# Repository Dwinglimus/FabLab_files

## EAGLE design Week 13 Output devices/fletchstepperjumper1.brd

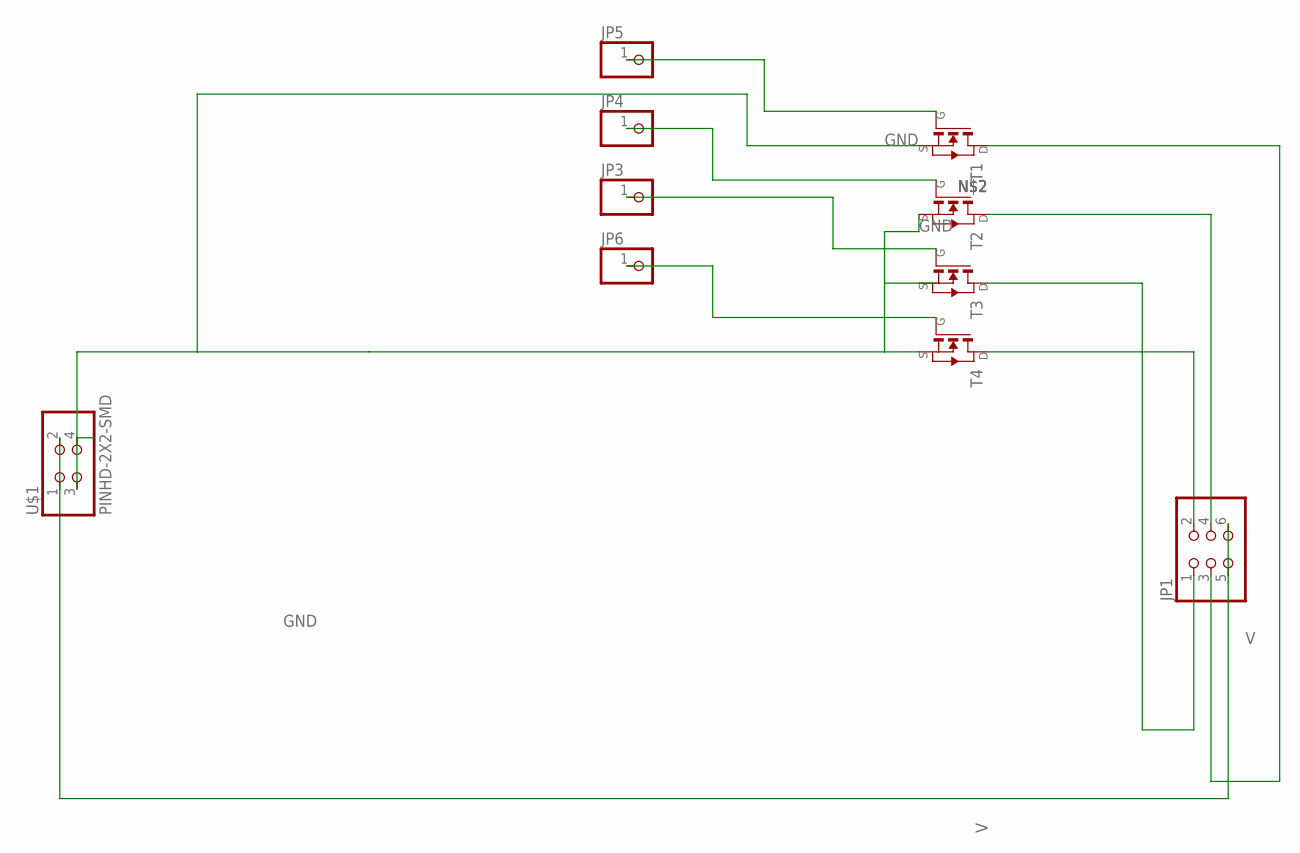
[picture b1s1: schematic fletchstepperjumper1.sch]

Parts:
JP1: PINHD-2X3-SMD; 2X03SMD
JP3, JP4, JP5, JP6: PINHD-1X1; 1X01
T1, T2, T3, T4: NMOSFETSOT23; SOT-23
U$1: PINHD-2X2-SMD; 2X02SMD

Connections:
GND: T1.2 (S), T2.2 (S), T4.2 (S), U$1.3
unnamed: JP6.1, T4.3 (G)
unnamed: JP4.1, T2.3 (G)
unnamed: JP3.1, T3.3 (G)
unnamed: JP1.2, T4.1 (D)
unnamed: JP1.4, T2.1 (D)
unnamed: JP1.1, T3.1 (D)
unnamed: JP1.3, T1.1 (D)
unnamed: JP5.1, T1.3 (G)
V: JP1.5, JP1.6, U$1.1, U$1.2

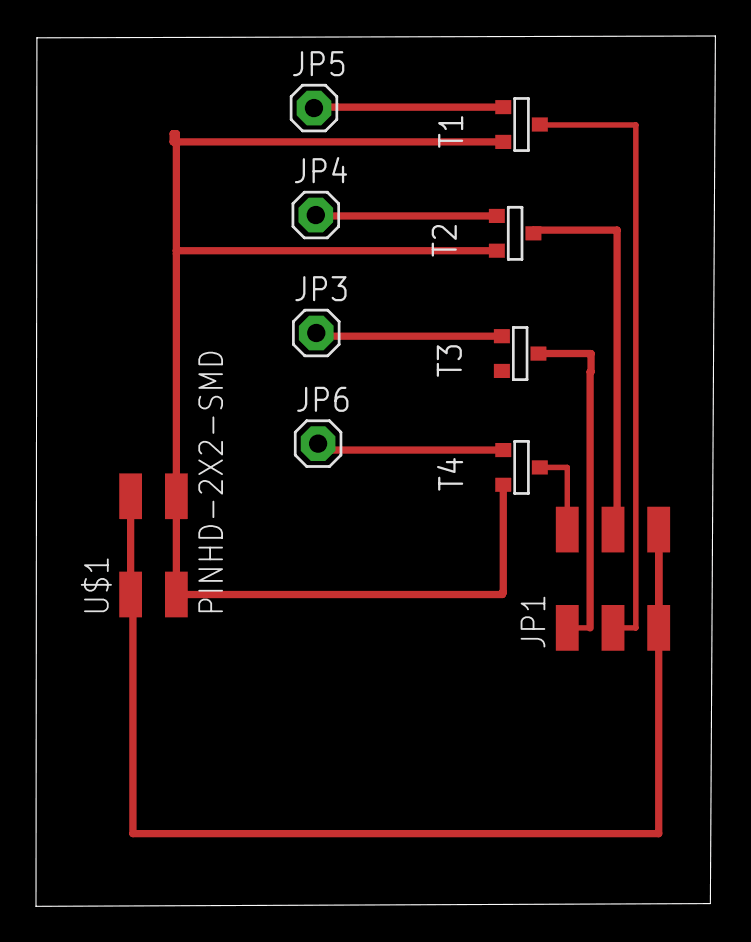
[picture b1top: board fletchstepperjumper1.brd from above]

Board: 2 copper layers, 37.7 x 48.4 mm, 10 parts (0 on the bottom side), 10 nets.

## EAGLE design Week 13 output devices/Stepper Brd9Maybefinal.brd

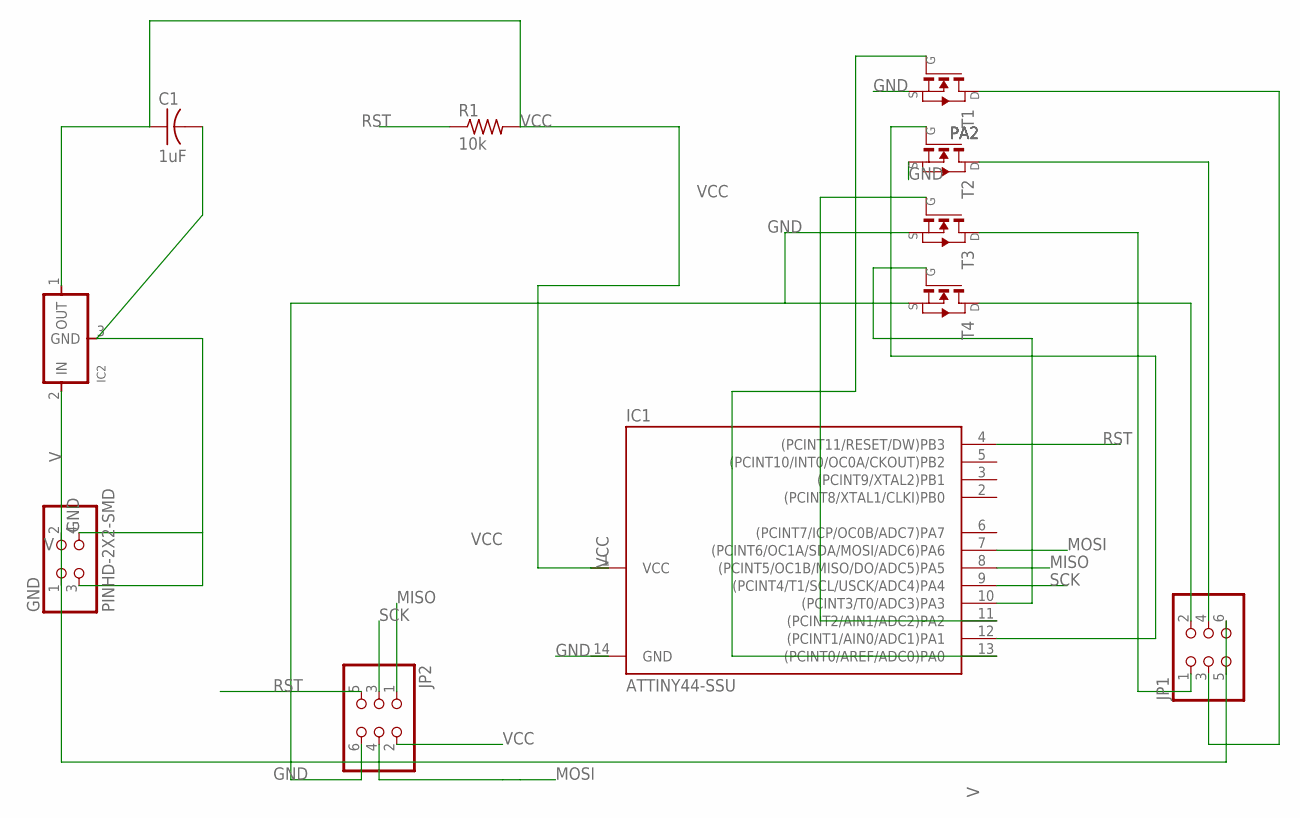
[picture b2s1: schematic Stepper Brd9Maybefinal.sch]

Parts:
C1: 1uF; C1206FAB
GND: PINHD-2X2-SMD; 2X02SMD
IC1: ATTINY44-SSU; SOIC14
IC2: REGULATORSOT23; SOT23
JP1, JP2: PINHD-2X3-SMD; 2X03SMD
R1: 10k; R1206FAB
T1, T2, T3, T4: NMOSFETSOT23; SOT-23

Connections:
GND: C1.2, GND.3, GND.4, IC1.14 (GND), IC2.3 (GND), JP2.6, T1.2 (S), T2.2 (S), T3.2 (S), T4.2 (S)
MISO: IC1.8 ((PCINT5/OC1B/MISO/DO/ADC5)PA5), JP2.1
MOSI: IC1.7 ((PCINT6/OC1A/SDA/MOSI/ADC6)PA6), JP2.4
unnamed: IC1.10 ((PCINT3/T0/ADC3)PA3), T4.3 (G)
unnamed: IC1.11 ((PCINT2/AIN1/ADC2)PA2), T3.3 (G)
unnamed: JP1.2, T4.1 (D)
unnamed: JP1.4, T2.1 (D)
unnamed: JP1.1, T3.1 (D)
unnamed: JP1.3, T1.1 (D)
unnamed: IC1.13 ((PCINT0/AREF/ADC0)PA0), T1.3 (G)
PA2: IC1.12 ((PCINT1/AIN0/ADC1)PA1), T2.3 (G)
RST: IC1.4 ((PCINT11/RESET/DW)PB3), JP2.5, R1.1
SCK: IC1.9 ((PCINT4/T1/SCL/USCK/ADC4)PA4), JP2.3
V: GND.1, GND.2, IC2.2 (IN), JP1.5, JP1.6
VCC: C1.1, IC1.1 (VCC), IC2.1 (OUT), JP2.2, R1.2

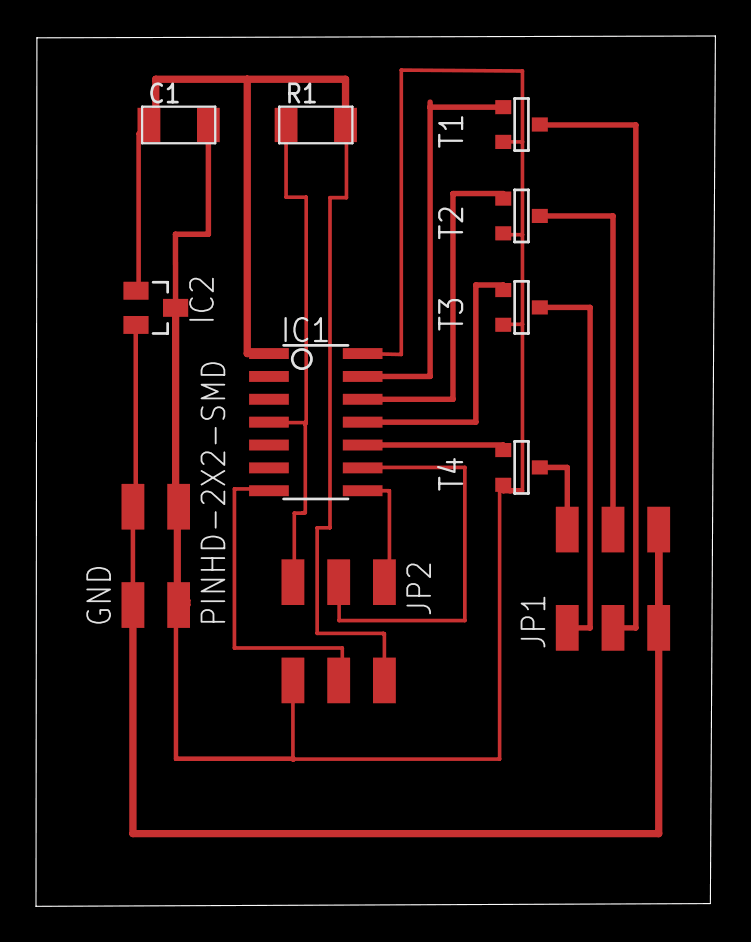
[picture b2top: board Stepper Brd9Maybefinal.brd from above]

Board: 2 copper layers, 37.7 x 48.4 mm, 11 parts (0 on the bottom side), 15 nets.

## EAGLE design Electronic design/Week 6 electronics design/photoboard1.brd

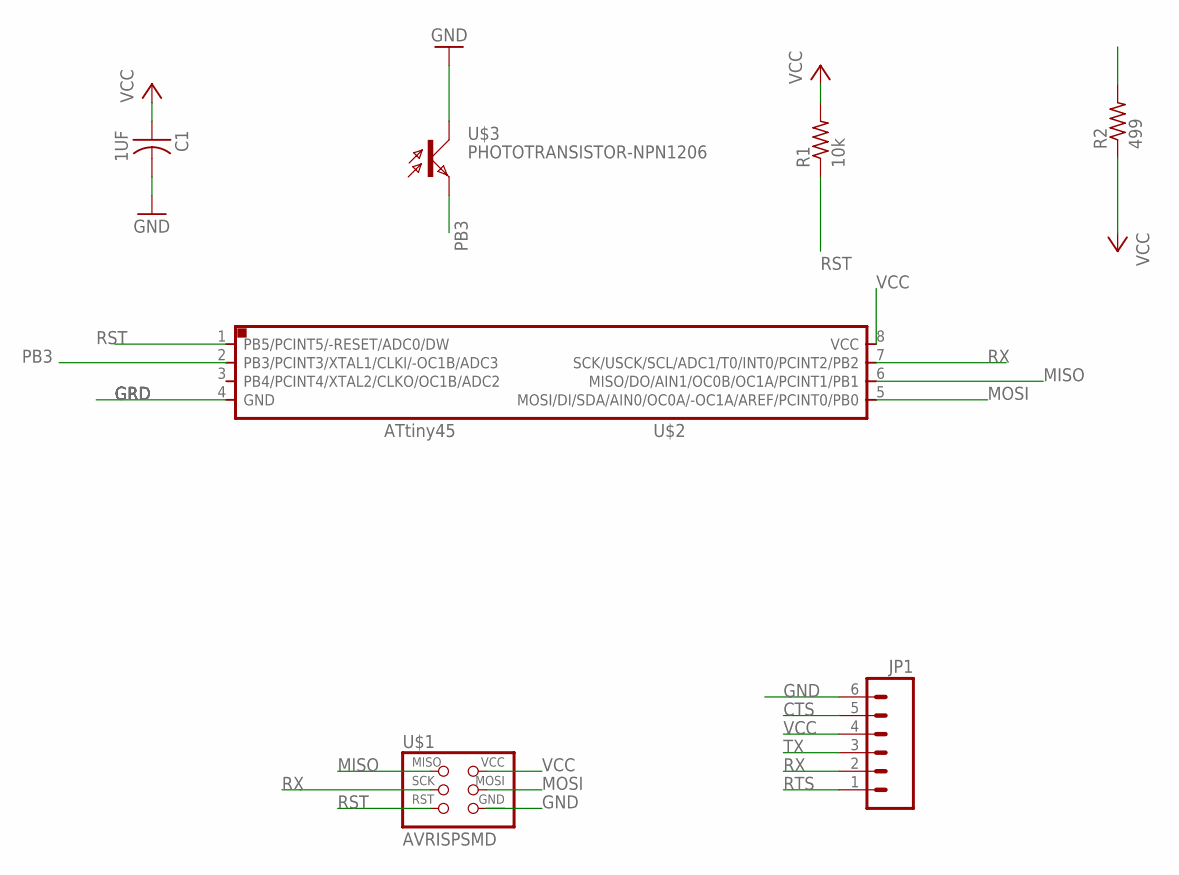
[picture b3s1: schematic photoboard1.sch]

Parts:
C1: 1UF; C1206FAB
JP1: M06SMD; 1X06-SMD
R1: 10k; R1206
R2: 499; R1206
U$1: AVRISPSMD; 2X03SMD
U$2: ATTINY45SI; SOIC8
U$3: PHOTOTRANSISTOR-NPN1206; OP1206

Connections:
CTS: JP1.5
GND: C1.2, JP1.6, U$1.6 (GND), U$3.COLLECTOR (C)
GRD: U$2.4 (GND)
MISO: U$1.1 (MISO), U$2.6 (MISO/DO/AIN1/OC0B/OC1A/PCINT1/PB1)
MOSI: U$1.4 (MOSI), U$2.5 (MOSI/DI/SDA/AIN0/OC0A/-OC1A/AREF/PCINT0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)
PB3: R2.2, U$2.2 (PB3/PCINT3/XTAL1/CLKI/-OC1B/ADC3), U$3.EMITTER (E)
RST: R1.1, U$1.5 (RST), U$2.1 (PB5/PCINT5/-RESET/ADC0/DW)
RTS: JP1.1
RX: JP1.2, U$1.3 (SCK), U$2.7 (SCK/USCK/SCL/ADC1/T0/INT0/PCINT2/PB2)
TX: JP1.3
VCC: C1.1, JP1.4, R1.2, R2.1, U$1.2 (VCC), U$2.8 (VCC)

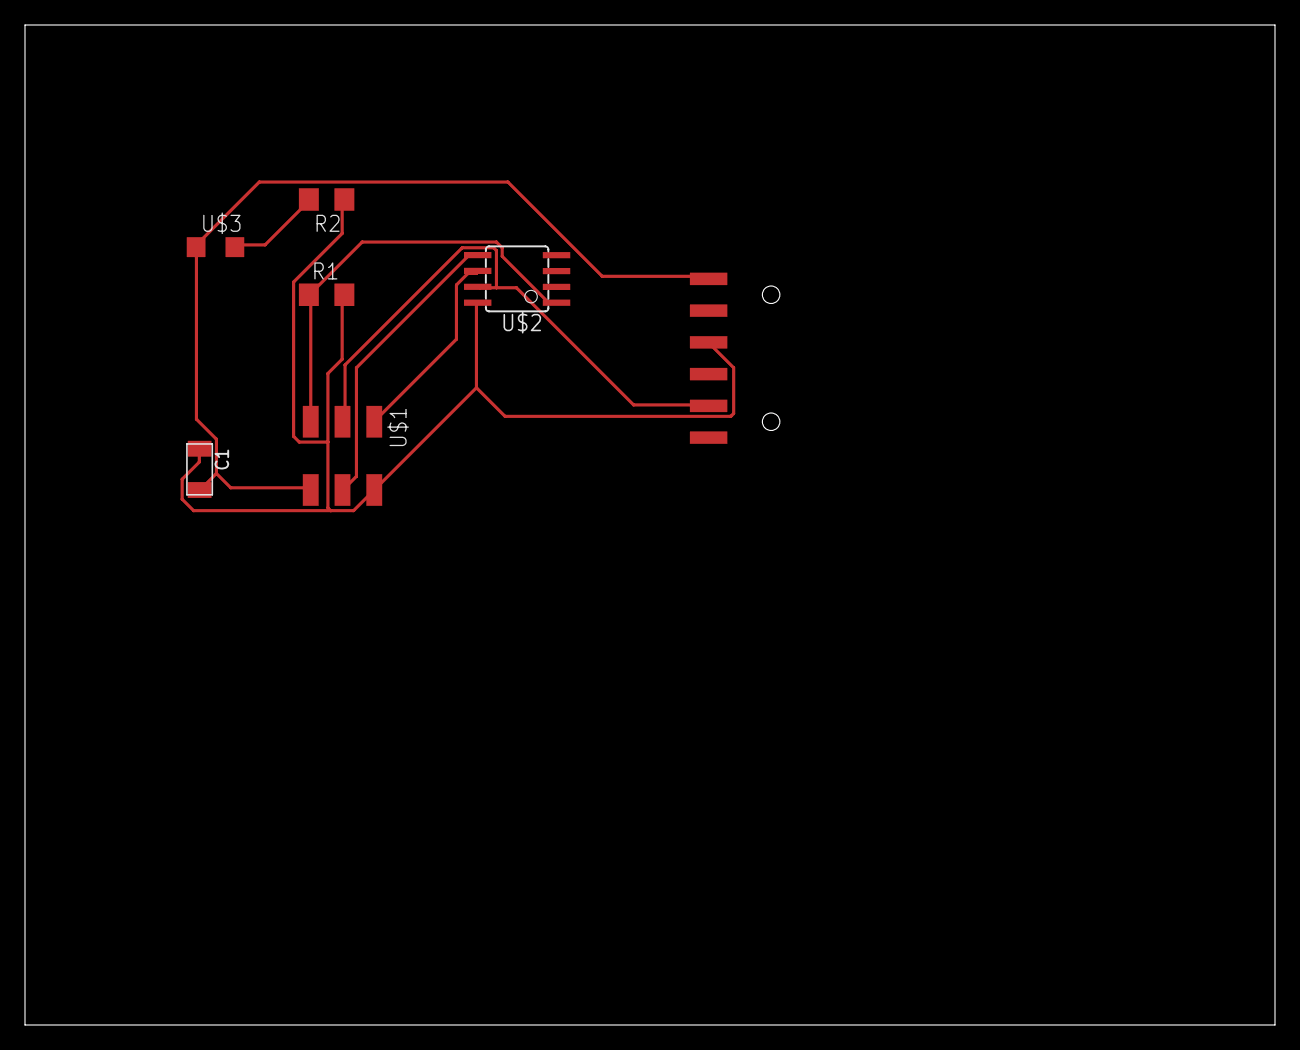
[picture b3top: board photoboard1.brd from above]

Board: 2 copper layers, 100.0 x 80.0 mm, 7 parts (0 on the bottom side), 7 nets.

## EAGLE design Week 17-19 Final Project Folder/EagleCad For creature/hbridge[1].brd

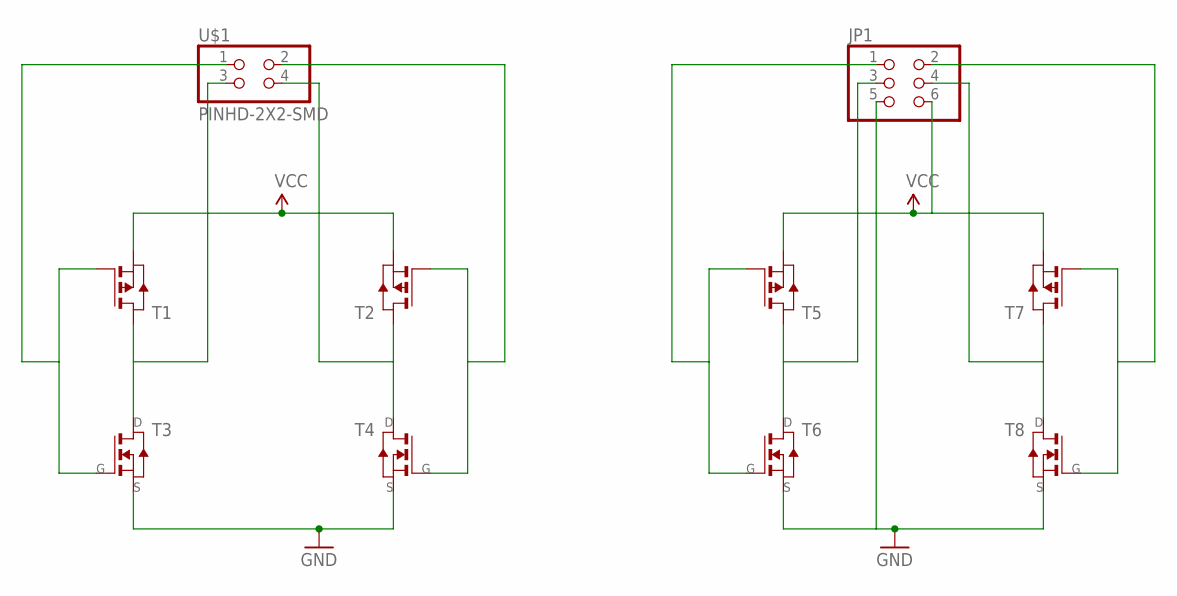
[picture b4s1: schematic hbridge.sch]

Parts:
JP1: PINHD-2X3-SMD; 2X03SMD
T1, T2, T5, T7: PMOSFETSOT23; SOT-23
T3, T4, T6, T8: NMOSFETSOT23; SOT-23
U$1: PINHD-2X2-SMD; 2X02SMD

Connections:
GND: JP1.5, T3.2 (S), T4.2 (S), T6.2 (S), T8.2 (S)
unnamed: T1.1 (D), T3.1 (D), U$1.3
unnamed: T2.1 (D), T4.1 (D), U$1.4
unnamed: T2.3 (G), T4.3 (G), U$1.2
unnamed: T1.3 (G), T3.3 (G), U$1.1
unnamed: JP1.3, T5.1 (D), T6.1 (D)
unnamed: JP1.4, T7.1 (D), T8.1 (D)
unnamed: JP1.2, T7.3 (G), T8.3 (G)
unnamed: JP1.1, T5.3 (G), T6.3 (G)
VCC: JP1.6, T1.2 (S), T2.2 (S), T5.2 (S), T7.2 (S)

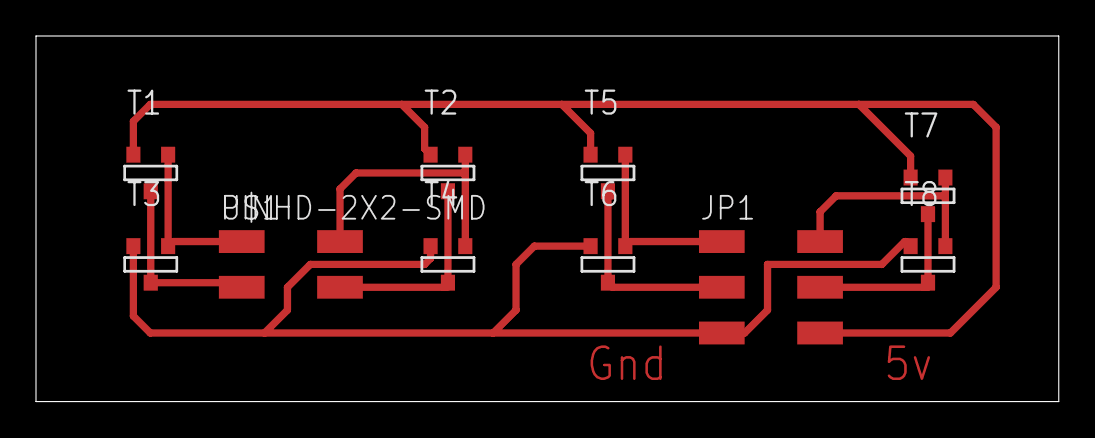
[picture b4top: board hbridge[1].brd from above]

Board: 2 copper layers, 56.8 x 20.3 mm, 10 parts (0 on the bottom side), 10 nets.

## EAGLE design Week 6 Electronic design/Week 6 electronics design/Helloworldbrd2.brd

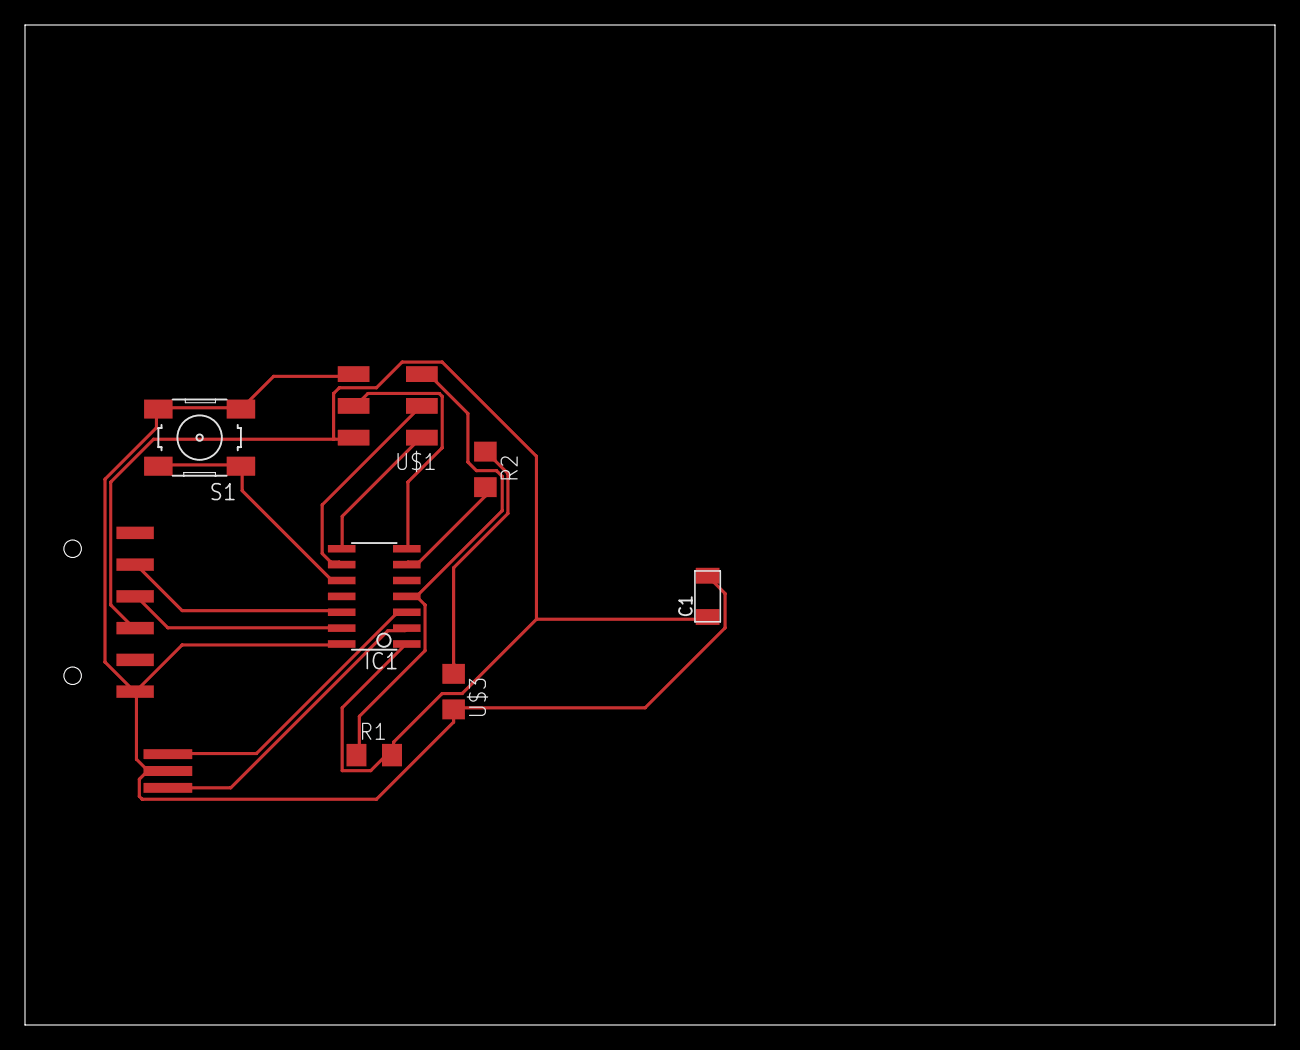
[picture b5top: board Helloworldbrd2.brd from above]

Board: 2 copper layers, 100.0 x 80.0 mm, 9 parts (0 on the bottom side), 13 nets.

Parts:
C1: 1UF; C1206FAB
IC1: ATTINY44-SSU; SOIC14
JP1: 1X06-SMD
R1: 10k; R1206
R2: 499; R1206
S1: 6MM_SWITCH
U$1: AVRISPSMD; 2X03SMD
U$2: RESONATOR; EFOBM
U$3: LED; LED1206

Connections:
BUTTON: IC1.10, S1.1, S1.2
GND: C1.2, IC1.14, JP1.6, S1.3, S1.4, U$1.6, U$2.2, U$3.2
LED: IC1.6, R2.2
MISO: IC1.8, U$1.1
MOSI: IC1.7, U$1.4
unnamed: IC1.2, U$2.1
unnamed: R2.1, U$3.1
unnamed: IC1.3, U$2.3
RST: IC1.4, R1.1, U$1.5
RX: IC1.12, JP1.2
SCK: IC1.9, U$1.3
TX: IC1.13, JP1.3
VCC: C1.1, IC1.1, JP1.4, R1.2, U$1.2

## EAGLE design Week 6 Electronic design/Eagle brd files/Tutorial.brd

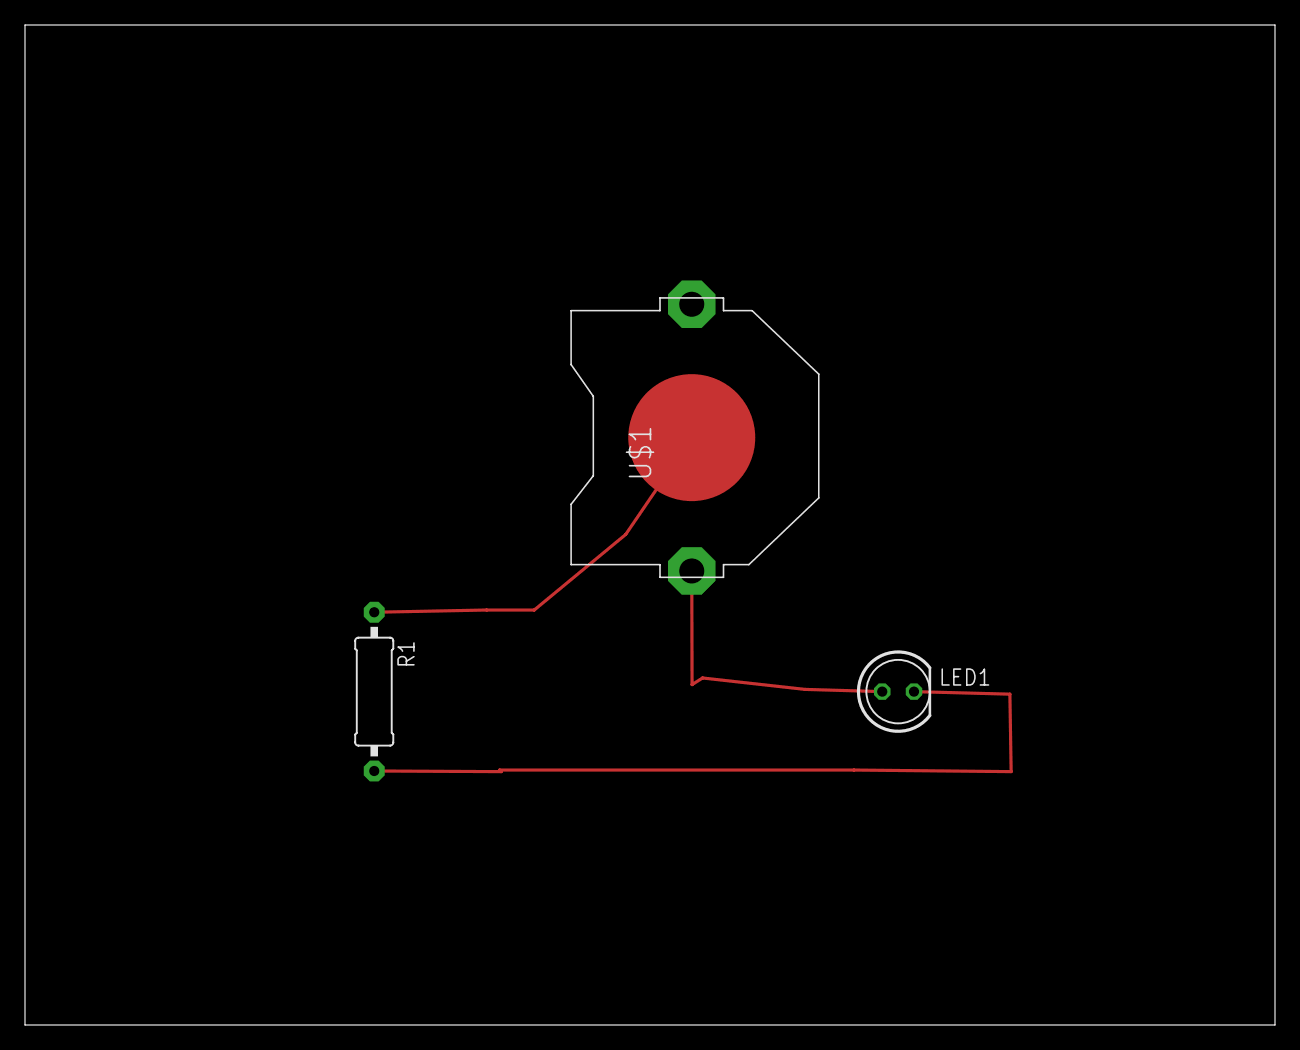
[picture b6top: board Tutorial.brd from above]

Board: 2 copper layers, 100.0 x 80.0 mm, 3 parts (0 on the bottom side), 3 nets.

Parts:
LED1: LED5MM
R1: 0309/12
U$1: CR2032-THRU

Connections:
unnamed: LED1.A, U$1.+1
unnamed: LED1.K, R1.2
unnamed: R1.1, U$1.-

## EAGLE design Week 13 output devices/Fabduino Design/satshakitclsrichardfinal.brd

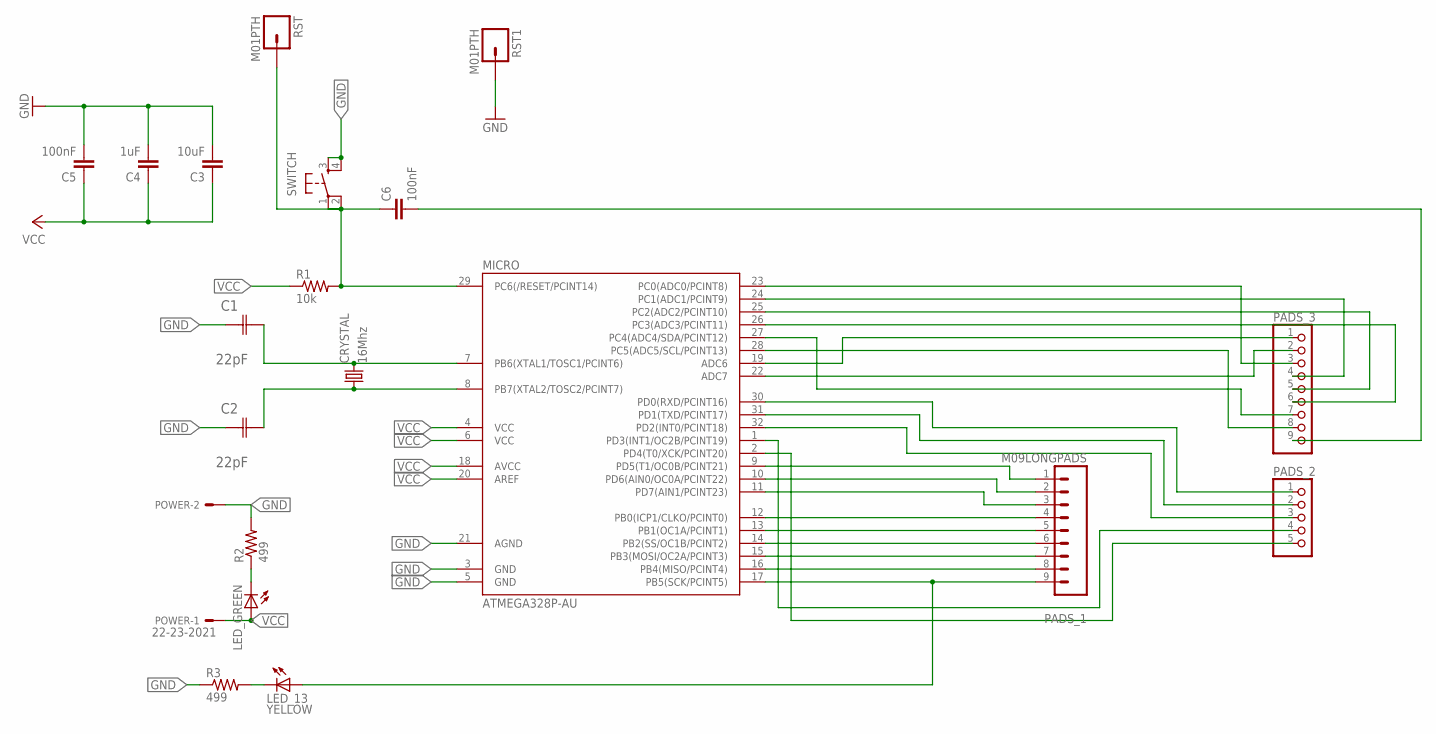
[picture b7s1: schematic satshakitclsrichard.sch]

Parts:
C1, C2: 22pF; CAPC3216X178N
C3: 10uF; 1206
C4: 1uF; 1206
C5, C6: 100nF; 1206
CRYSTAL: 16Mhz; CSM-7X-DU
LED_13: YELLOW; 1206
LED_GREEN: LED1206; 1206
MICRO: ATMEGA328P-AU; TQFP32-08
PADS_1: M09LONGPADS; 1X09_LONGPADS
PADS_2: PINHD-1X5; 1X05
PADS_3: PINHD-1X9; 1X09
POWER: 22-23-2021
R1: 10k; 1206
R2, R3: 499; 1206
RST, RST1: M01PTH; 1X01
SWITCH: 6MM_SWITCH6MM_SWITCH; 6MM_SWITCH

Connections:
GND: C1.1 (C1), C2.1 (C1), C3.2, C4.2, C5.2, MICRO.3 (GND), MICRO.5 (GND), MICRO.21 (AGND), POWER.2, R2.2, R3.1, RST1.1, SWITCH.3 (S), SWITCH.4 (S1)
unnamed: MICRO.9 (PD5(T1/OC0B/PCINT21)), PADS_1.1
unnamed: C1.2 (C2), CRYSTAL.2, MICRO.7 (PB6(XTAL1/TOSC1/PCINT6))
unnamed: C6.2, PADS_3.9
unnamed: MICRO.10 (PD6(AIN0/OC0A/PCINT22)), PADS_1.2
unnamed: MICRO.11 (PD7(AIN1/PCINT23)), PADS_1.3
unnamed: MICRO.12 (PB0(ICP1/CLKO/PCINT0)), PADS_1.4
unnamed: MICRO.13 (PB1(OC1A/PCINT1)), PADS_1.5
unnamed: MICRO.14 (PB2(SS/OC1B/PCINT2)), PADS_1.6
unnamed: C2.2 (C2), CRYSTAL.1, MICRO.8 (PB7(XTAL2/TOSC2/PCINT7))
unnamed: MICRO.15 (PB3(MOSI/OC2A/PCINT3)), PADS_1.7
unnamed: MICRO.16 (PB4(MISO/PCINT4)), PADS_1.8
unnamed: LED_13.1 (A), MICRO.17 (PB5(SCK/PCINT5)), PADS_1.9
unnamed: MICRO.19 (ADC6), PADS_3.1
unnamed: MICRO.22 (ADC7), PADS_3.2
unnamed: MICRO.23 (PC0(ADC0/PCINT8)), PADS_3.3
unnamed: MICRO.24 (PC1(ADC1/PCINT9)), PADS_3.4
unnamed: MICRO.25 (PC2(ADC2/PCINT10)), PADS_3.5
unnamed: MICRO.26 (PC3(ADC3/PCINT11)), PADS_3.6
unnamed: MICRO.27 (PC4(ADC4/SDA/PCINT12)), PADS_3.7
unnamed: MICRO.30 (PD0(RXD/PCINT16)), PADS_2.1
unnamed: MICRO.31 (PD1(TXD/PCINT17)), PADS_2.2
unnamed: MICRO.32 (PD2(INT0/PCINT18)), PADS_2.3
unnamed: MICRO.1 (PD3(INT1/OC2B/PCINT19)), PADS_2.4
unnamed: MICRO.2 (PD4(T0/XCK/PCINT20)), PADS_2.5
unnamed: MICRO.28 (PC5(ADC5/SCL/PCINT13)), PADS_3.8
unnamed: LED_GREEN.2 (C), R2.1
unnamed: LED_13.2 (C), R3.2
unnamed: C6.1, MICRO.29 (PC6(/RESET/PCINT14)), R1.2, RST.1, SWITCH.1, SWITCH.2 (P1)
VCC: C3.1, C4.1, C5.1, LED_GREEN.1 (A), MICRO.4 (VCC), MICRO.6 (VCC), MICRO.18 (AVCC), MICRO.20 (AREF), POWER.1, R1.1

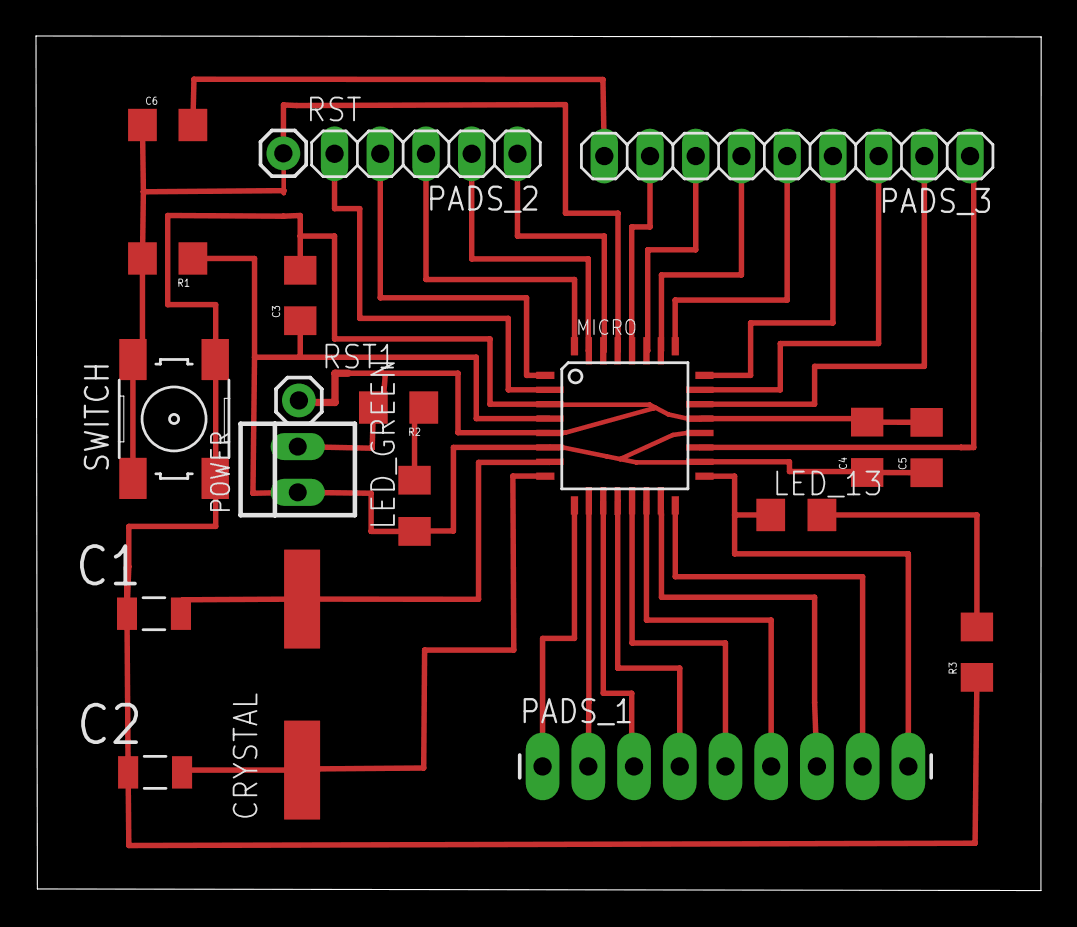
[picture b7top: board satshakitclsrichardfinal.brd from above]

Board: 2 copper layers, 55.8 x 47.5 mm, 20 parts (0 on the bottom side), 30 nets.

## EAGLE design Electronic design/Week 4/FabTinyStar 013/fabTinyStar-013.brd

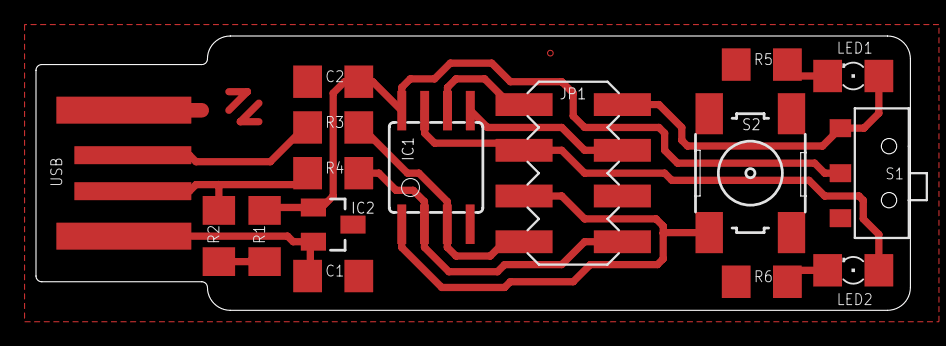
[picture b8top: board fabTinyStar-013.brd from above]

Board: 2 copper layers, 48.6 x 15.2 mm, 16 parts (0 on the bottom side), 15 nets.

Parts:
C1: 10uF; 1206
C2: 100nF; 1206
IC1: ATTINY*5; SOIC8
IC2: 3v3; SOT23
JP1: PINHD-2X04; 54202-G0808LF
LED1: red; 1206
LED2: green; 1206
R1, R5: 1K; 1206
R2, R6: 499; 1206
R3, R4: 49; 1206
S1: SLIDE-SWITCH; AYZ0102AGRLC
S2: 6MM_SWITCH
USB: USBPCB; USB-A-PCB

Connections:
5V: C1.1, IC2.2, USB.5V
B3: IC1.2, JP1.8, R4.2
B4: IC1.3, JP1.7, R3.2
D+: R3.1, USB.USB_P
D-: R2.1, R4.1, USB.USB_M
GND: C1.2, C2.1, IC1.4, IC2.3, JP1.6, R5.2, R6.2, S2.3, S2.4, USB.GND
MISO: IC1.6, JP1.1
MOSI: IC1.5, JP1.4
unnamed: R1.2, R2.2
unnamed: LED2.C, R6.1
unnamed: LED1.C, R5.1
RESET: IC1.1, JP1.5, S2.1
SCK: IC1.7, JP1.3, LED2.A
TP: JP1.2, LED1.A, S1.3
VCC: C2.2, IC1.8, IC2.1, R1.1, S1.2

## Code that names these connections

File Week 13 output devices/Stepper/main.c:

include <avr/io.h>
#include <util/delay.h>

#define output(directions,pin) (directions |= pin) // set port direction for output
#define set(port,pin) (port |= pin) // set port pin
#define clear(port,pin) (port &= (~pin)) // clear port pin
#define pin_test(pins,pin) (pins & pin) // test for port pin
#define bit_test(byte,bit) (byte & (1 << bit)) // test for bit set

#define MOSFET_port PORTA // MOSFET port
#define MOSFET_direction DDRA // MOSFET direction
#define brown (1 << PA0) // MOSFET output pins
#define black (1 << PA1) // "
#define yellow (1 << PA2) // "
#define orange (1 << PA3) // "
#define on_delay() _delay_us(50) // PWM on time
#define off_delay() _delay_us(10) // PWM off time
#define PWM_count 200 // number of PWM cycles

static uint8_t count;

//
// yellow, brown PWM pulse
//
void pulse_yellow_brown() {
   for (count = 0; count < PWM_count; ++count) {
      set(MOSFET_port, yellow);
      set(MOSFET_port, brown);
      on_delay();
      clear(MOSFET_port, yellow);
      clear(MOSFET_port, brown);
      off_delay();
      }
   }
//
// yellow, black PWM pulse
//
void pulse_yellow_black() {
   for (count = 0; count < PWM_count; ++count) {
      set(MOSFET_port, yellow);
      set(MOSFET_port, black);
      on_delay();
      clear(MOSFET_port, yellow);
      clear(MOSFET_port, black);
      off_delay();
      }
   }
//
// orange, brown PWM pulse
//
void pulse_orange_brown() {
   for (count = 0; count < PWM_count; ++count) {
      set(MOSFET_port, orange);
      set(MOSFET_port, brown);
      on_delay();
      clear(MOSFET_port, orange);
      clear(MOSFET_port, brown);
      off_delay();
      }
   }
//
// orange, black PWM pulse
//
void pulse_orange_black() {
   for (count = 0; count < PWM_count; ++count) {
      set(MOSFET_port, orange);
      set(MOSFET_port, black);
      on_delay();
      clear(MOSFET_port, orange);
      clear(MOSFET_port, black);
      off_delay();
      }
   }
//
// clockwise step
//
void step_cw() {
   pulse_yellow_brown();
   pulse_yellow_black();
   pulse_orange_black();
   pulse_orange_brown();
   }
//
// counter-clockwise step
//
void step_ccw() {
   pulse_orange_brown();
   pulse_orange_black();
   pulse_yellow_black();
   pulse_yellow_brown();
   }

int main(void) {
   //
   // main
   //
   static uint8_t i,j;
   //
   // set clock divider to /1
   //
   CLKPR = (1 << CLKPCE);
   CLKPR = (0 << CLKPS3) | (0 << CLKPS2) | (0 << CLKPS1) | (0 << CLKPS0);
   //
   // initialize MOSFET pins
   //
   clear(MOSFET_port, brown);
   output(MOSFET_direction, brown);
   clear(MOSFET_port, black);
   output(MOSFET_direction, black);
   clear(MOSFET_port, yellow);
   output(MOSFET_direction, yellow);
   clear(MOSFET_port, orange);
   output(MOSFET_direction, orange);
   //
   // main loop
   //
   while (1) {
      for (i = 0; i < 10; ++i) {
         for (j = 0; j < i; ++j)
            step_cw();
         for (j = 0; j < i; ++j)
            step_ccw();
         }
      for (i = 10; i > 0; --i) {
         for (j = 0; j < i; ++j)
            step_cw();
         for (j = 0; j < i; ++j)
            step_ccw();
         }
      }
   }

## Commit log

2016-02-09 Antimony Files
2016-02-10 Sculptris Changes
2016-02-15 Weekend work
2016-02-29 3-D scanning and printing
2016-03-09 Electronic design
2016-03-16 ShowBot files
2016-03-30 NewEaglefiles
2016-04-06 More electronics
2016-04-13 Week9 machine files
2016-04-22 week10
2016-04-25 Week11 input
2016-05-22 Git update
2016-06-07 week 13 output
2016-06-07 stepper
2016-06-09 moreweek13 output
2016-06-13 Final Project Folder
2016-06-21 Cleaning up and final project
2016-06-23 Finalprojectfiles
2016-06-28 Week 8
2016-06-28 eagleweek8
2016-06-29 Cleaning up
2016-07-03 TheGruetestcode
2016-07-03 EaglecadHbridgeforfinal
2016-07-04 Networking
2016-07-07 Still cleaning up
2016-07-07 FinalProject organizing
2016-07-07 Still updating
2016-07-08 fusion360
2016-07-08 Creature rod
2016-07-26 embedded programming again
2016-07-26 More,more embedded programming

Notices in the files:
Electronic design/Week 4/FabTinyStar 013/fabTinyStar-013.brd:
CC BY-NC-SA 4.0
parts and their libraries:
SparkFun: Licensing: CC v3.0 Share-Alike You are welcome to use this library for commercial purposes.
